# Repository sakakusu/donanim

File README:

githubı çözene kadar hiyerarşi yanlış olabilir.

ultrasonik yaklaşım sensörleri ile başlıyorum

**** ultra.png **** 
toplam 8 sensör olacak
Texas int firmasının PGA460-q1 çipini sensörü sürmek ve eko yu yeniden okumak için kullanacağım 
eğer istediğim doğruluğu alamazsam stm32l443 ile yeniden çizeceğim baskı devre basılıp gelene kadarki çizim ultra.kicad_sch dosyasının içinde
deneyebilmek için pcd sini de hazırlayacağım pcb si ultra.kicad.pcb dosyasının içinde çizim tahminen 3 ocak 24 te yüklenmiş olur

kısaca devre elemanlarını tanıtayım 
aşağıda analog mux var 24V a kadar multiplex yapıp yeni çip daha önemlisi kapasite ve ağır trafo kullanımını azaltıyor
MUX4051 i 24V la sürüp adres pinini 3.3 ile süreceğiz

devre üzerinde üç ayrı ground var bunları çizim yaparken kolaylık olsun diye çizdim çizim işim bitince tek noktada birleştireceğim 
pcb çizerken video çekebilirsem videoda sebeplerini anlatırım video çekemezsen daha detaylı resimlerle açıklarım
ultra kısmının maliyeti 6 usd civarı.

****** gyro.png ****
ikinci kısım navigasyon, manyetik sensör, gyro, accelerometre, sıcaklık sensörü ve barometre
manyetik sensör kuzeyi bulmak için(1g yi geçmeyeceğimiz için yer çekimini ölçmeden nümerik olarak hesaplayacağım
sıcaklık sensörü; manyetik sensörü kalibre etmek için manyetik alan ölçen sensörler sıcaklıktan daha fazla etkilenirler
60 dolara heading açısının doğruluğu 0.01 derece olan çip vardı, hobi projesi olduğu için daha ucuz bir alternatif seçtim
doğruluğu 0.05 derece.

BNO085 çipi accelerormeter, gyro, ve sıcaklık sensörü bulunduruyor
BME280 barometre  maalesef bosch ancak ucuz ve iş görüyor kullandım

navigasyon kısmı çok detaylı izaha muhtaç 
NEO M8Q 01A seçtim arabalar için imal edilmiş düşük sıcaklıkta halen doğru ölçer, hobi projesi ne kadar bu sınırlara ihtiyaç duyar 
sizin kararınız fork yaparsanız pin to pin ucuz muadilleri yine ublox ta var birini kullanın
bulutlu havalarda navigasyon yavaşlamasın diye antende kuvvetlendirici ve bir saw filtre kullandım 
murata filtre digikeyde yoktu ürün temini ile uğraşmayayım diye maalesef stokta olan infineon kullandım 
kimse kullanmayınca stok bize kalmış elemanların değerlerinin hesabını video çekersem anlatırım vakit 
bulamazsam yeni bir yazı hazırlayacağım çizim üzerinde tanıtmadığım işlemci kaldı 
kalman filtre hesaplayacağım ana işlemciye iletişim için yük düşmesin kalman filtreyi hesaplasın
istendiğinde matris halinde ultrasoniklerden uzaklıkları, navigasyonu gyro accel barometrik sensörleri tek parçada göndersin diye ekledim
80 Mhz ye çıkabiliyor elimde var diye seçtim texas işlemcisi olsa daha iyi olurdu hobi projesi olduğu için st de olsa çizdim
çizimdeki üçüncü avrupa malı ürün oldu maalesef. boş bir vakitte üçünü de amerikan muadilleri ile değiştiririm. 
100 pinli ürünü seçme sebebim; elimde çokça numune var, atmayayım bari quadcopter olsun.

*** mcu_port.png ***
içerisinde seçili portlar var bu sıralamaya göre mcu bağlantılarını yapacağım 
3 spi bir i2c bir usb dac adc vs açtım kullanılmayan portları yazılımla kapatacağım
kicaddeli şema kütüphanesini buna göre güncelledim

imu donanımı bitti 
1- motor sürücü 
2- single board computer nxp imx8 ile
3- güç yönetimi, şarj ve deşarj yönetimi 
devresi hazırladıktan sonra baskı devreleri tek kart olarak yeniden çizeceğim aşama aşama programlarını yüklerim
4-iletişim kısmını hazır alacağım proje bitmeden(6 aydan kısa sürer) birkaç kişi talep ederse kriptolu ferkans atlamalı bir şey de tasarlayabilirim 

3 unde yüklerim yazmıştım masaüstü bilgisayarı açamadım yüklemem gecikti 

mcu ile çalıştırdıktan sonra fpga ile yeniden hazırlamayı düşünüyordum 50 dolar giriş seviyesi artix7 bu sebeple burası sadece mcu olarak kalacak 
kalman filtresi de mcu da çalışacak yeniden çizmeyeceğim belki enerji uçuş birleştirip tek çip yaparım board imu.kica_brd dosyasının içinde
bir tane dizip fotoğraf yüklerim kalman yazması uzun sürmez ama denemesi vakit alır mart başı umarım

iki tasarım eş zamanlı yapacağım bir tanesi hızlı bir tanesi sessiz
motor sürücüyü de ben tasarlayacağım o zaman detaylarıyla anlatırım
sonraki metinleri oku1- oku2 isimli dosyalarda yazacağım

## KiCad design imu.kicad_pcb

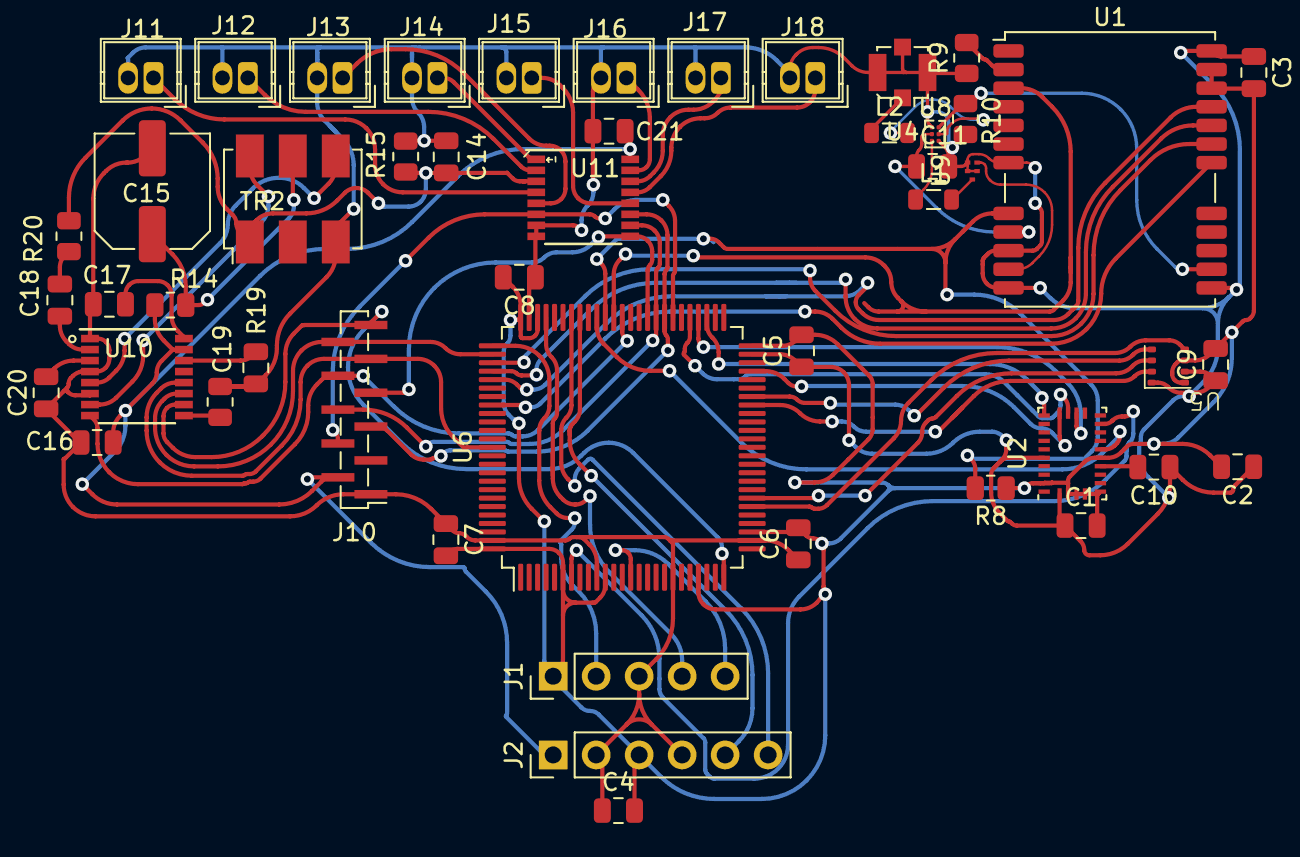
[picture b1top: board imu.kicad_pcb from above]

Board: 2 copper layers, 49 parts (0 on the bottom side), 59 nets.

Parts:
C1, C2, C3, C4, C5, C6, C7, C8, C9, C10, C16, C17, C19, C21: 100nF; C_0805_2012Metric
C11: 33nF; C_0805_2012Metric
C14: 3.9nF 100V; C_0805_2012Metric
C15: 100uF. 35V; C_Elec_6.3x7.7
C18: 330pF 100V; C_0805_2012Metric
C20: 33pF; C_0805_2012Metric
J1: Conn_01x05_Pin; PinHeader_1x05_P2.54mm_Vertical
J2: Conn_01x06_Pin; PinHeader_1x06_P2.54mm_Vertical
J10: Conn_01x11_Socket; PinSocket_1x11_P1.00mm_Vertical_SMD_Pin1Left
J11, J12, J13, J14, J15, J16, J17, J18: Conn_01x02; Wuerth_WR-WTB_64800211622_1x02_P1.50mm_Vertical
L1: 3.9nH; L_0805_2012Metric
L2: 12nH; L_0805_2012Metric
R8, R9, R19: 1K; R_0805_2012Metric
R10: 10K; R_0805_2012Metric
R14: 0R; R_0805_2012Metric
R15: 3.9K; R_0805_2012Metric
R20: 100R; R_0805_2012Metric
TR2: B78416A2232A003; Mini-Circuits_CD542_H2.84mm
U1: ublox_NEO
U2: LGA-28_5.2x3.8mm_P0.5mm
U4: U.FL_Molex_MCRF_73412-0110_Vertical
U5: BME280
U6: LQFP-100_14x14mm_P0.5mm
U8: Infineon_PG-TSNP-6-10_0.7x1.1mm_0.7x1.1mm_P0.4mm
U9: SAW_FILTER
U10, U11: HTSSOP-16-1EP_4.4x5mm_P0.65mm_EP3.4x5mm

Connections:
4051_A0: J10.5, U6.58 (PD11), U11.11 (A0)
4051_A1: J10.6, U6.59 (PD12), U11.10 (A1)
4051_A2: J10.7, U6.60 (PD13), U11.9 (A2)
4051_EN: J10.4, U6.57 (PD10), U11.6 (EN)
+3.3V: C1.2, C2.2, C3.2, C4.2, C5.2, C6.2, C7.2, C8.2, C9.2, J1.1, J2.3, R8.1, U1.22 (V_BCKP), U1.23 (VCC), U2.3 (VDD), U2.4 (BOOT_N), U2.5 (PS1), U2.6 (PS0), U2.10 (CLK_SEL0), U2.28 (VDD), U5.6 (VDD), U5.8 (VDD), U6.6 (VBAT), U6.11 (VDD), U6.22 (VDDA), U6.28 (VDD), U6.50 (VDD), U6.73 (VDDUSB), U6.75 (VDD), U6.100 (VDD)
/nav/1SEC_PULSE: U1.3 (TIME_PULSE), U6.64 (PC7)
/nav/ANT_OFF: R10.2, U1.14 (ANT_OFF), U8.6 (PON)
/nav/BME280_CSB: U5.2 (CSB), U6.43 (PE12)
/nav/BME280_SCK: U5.4 (SCK), U6.44 (PE13/SPI1_SCK)
/nav/BME280_SDI: U5.3 (SDI), U6.32 (PA7/SPI1_MOSI)
/nav/BME280_SDO: U5.5 (SDO), U6.31 (PA6/SPI1_MISO)
/nav/BNO085_CS: U2.18 (SPI_CS), U6.55 (PD8)
/nav/BNO085_INT: U2.14 (INT), U6.7 (PC13)
/nav/BNO085_MISO: U2.20 (SPI_MISO), U6.53 (PB14/SPI2_MISO)
/nav/BNO085_MOSI: U2.17 (SPI_MOSI), U6.54 (PB15/SPI2_MOSI)
/nav/BNO085_RST: U2.11 (NRST), U6.66 (PC9)
/nav/BNO085_SCL: U2.19 (SPI_SCL), U6.47 (PB10/SPI2_SCK)
/nav/DEBUG_RX: J2.5, U6.68 (PA9/USART1_TX)
/nav/DEBUG_TX: J2.6, U6.69 (PA10/USART1_RX)
/nav/MCU_RESET: J1.5, U6.14 (NRST)
/nav/MCU_SWCLK: J1.2, U6.76 (PA14/SWCLK)
/nav/MCU_SWDIO: J1.4, U6.72 (PA13/SWDIO)
/nav/NEO_RST: R8.2, U1.8 (RESET_N), U6.65 (PC8)
/nav/NEO_SPI_CSN: U1.18 (SPI_CSN), U6.83 (PD2)
/nav/NEO_SPI_MISO: U1.20 (SPI_MISO), U6.79 (PC11/SPI3_MISO)
/nav/NEO_SPI_MOSI: U1.21 (SPI_MOSI), U6.80 (PC12/SPI3_MOSI)
/nav/NEO_SPI_SCLK: U1.19 (SPI_CLK), U6.78 (PC10/SPI3_SCK)
/nav/VCC_ANT: C11.2, U1.9 (VCC_RF), U8.2 (VCC)
/ultra/RTRN_ULT: C14.1, R15.1, R20.2, TR2.1, U11.3 (D)
/ultra/ULT_OUT_A: TR2.4, U10.5 (OUTA)
/ultra/ULT_OUT_B: TR2.6, U10.7 (OUTB)
unnamed: C15.1, R14.2, TR2.5
unnamed: C18.2, R20.1
unnamed: J11.1, U11.4 (S7)
unnamed: J12.1, U11.2 (S6)
unnamed: J13.1, U11.5 (S5)
unnamed: J14.1, U11.1 (S4)
unnamed: J15.1, U11.12 (S3)
unnamed: J16.1, U11.15 (S2)
unnamed: J17.1, U11.14 (S1)
unnamed: J18.1, U11.13 (S0)
unnamed: R9.2, U1.2 (D_SEL)
unnamed: U1.11 (RF_IN), U9.4 (OUT)
unnamed: C10.2, U2.9 (CAP)
unnamed: L2.1, U4.1 (RF_IN)
unnamed: L2.2, U8.5 (AI)
unnamed: L1.1, U8.3 (AO)
unnamed: L1.2, U9.1 (IN)
unnamed: C17.1, U10.16 (AVDD)
unnamed: C20.2, U10.3 (INN)
unnamed: C18.1, U10.2 (INP)
unnamed: C19.2, U10.14 (IOREG)
unnamed: R19.1, U10.9 (TEST)
ULT_24: C16.2, C21.2, J2.1, J10.2, R14.1, U10.15 (VPWR), U11.16 (VDD)
ULT_GND: C1.1, C2.1, C3.1, C4.1, C5.1, C6.1, C7.1, C8.1, C9.1, C10.1, C11.1, C14.2, C15.2, C16.1, C17.2, C19.1, C20.1, C21.1, J1.3, J2.2, J2.4, J10.1, J11.2, J12.2, J13.2, J14.2, J15.2, J16.2, J17.2, J18.2, R9.1, R10.1, R15.2, R19.2, TR2.3, U1.7 (VDD_USB), U1.10 (GND), U1.12 (GND), U1.13 (GND), U1.24 (GND), U2.2 (GND), U2.25 (GND), U4.2 (GND), U5.1 (GND), U5.7 (GND), U6.10 (VSS), U6.19 (VSSA), U6.27 (VSS), U6.49 (VSS), U6.74 (VSS), U6.99 (VSS), U8.1 (GND), U8.4 (GNDRF), U9.2 (GND), U9.3 (GND), U9.5 (GND), U10.1 (GND), U10.4 (GND), U10.6 (GNDP), U11.7 (VSS), U11.8 (GND)
ULT_OWB: J10.8, U6.63 (PC6), U10.8 (IO)
ULT_RXD: J10.11, U6.25 (PA2/USART2_TX), U10.10 (TXD)
ULT_SCK: J10.9, U6.88 (PD7/USART2_CK), U10.12 (SCK)
ULT_TXD: J10.10, U6.77 (PA15/USART2_RX), U10.11 (RXD)
